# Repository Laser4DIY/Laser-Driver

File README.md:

# LASER4DIY Laser Diode Driver

Constant current power supply for laser diode to be used for the Laser4DIY project, see http://www.laser4diy.org/

Note: we are currently developing a new improved version of the laser diode driver, see https://github.com/Laser4DIY/Laser-Driver-v2

Copyright FabLab München e.V.  2021.

This source describes Open Hardware and is licensed under the CERN-OHL-P v2

You may redistribute and modify this documentation and make products using it 
under the terms of the CERN-OHL-P v2 (https:/cern.ch/cern-ohl).
This documentation is distributed WITHOUT ANY EXPRESS OR IMPLIED WARRANTY, 
INCLUDING OF MERCHANTABILITY, SATISFACTORY QUALITY AND FITNESS FOR A  PARTICULAR 
PURPOSE. Please see the CERN-OHL-P v2 for applicable conditions

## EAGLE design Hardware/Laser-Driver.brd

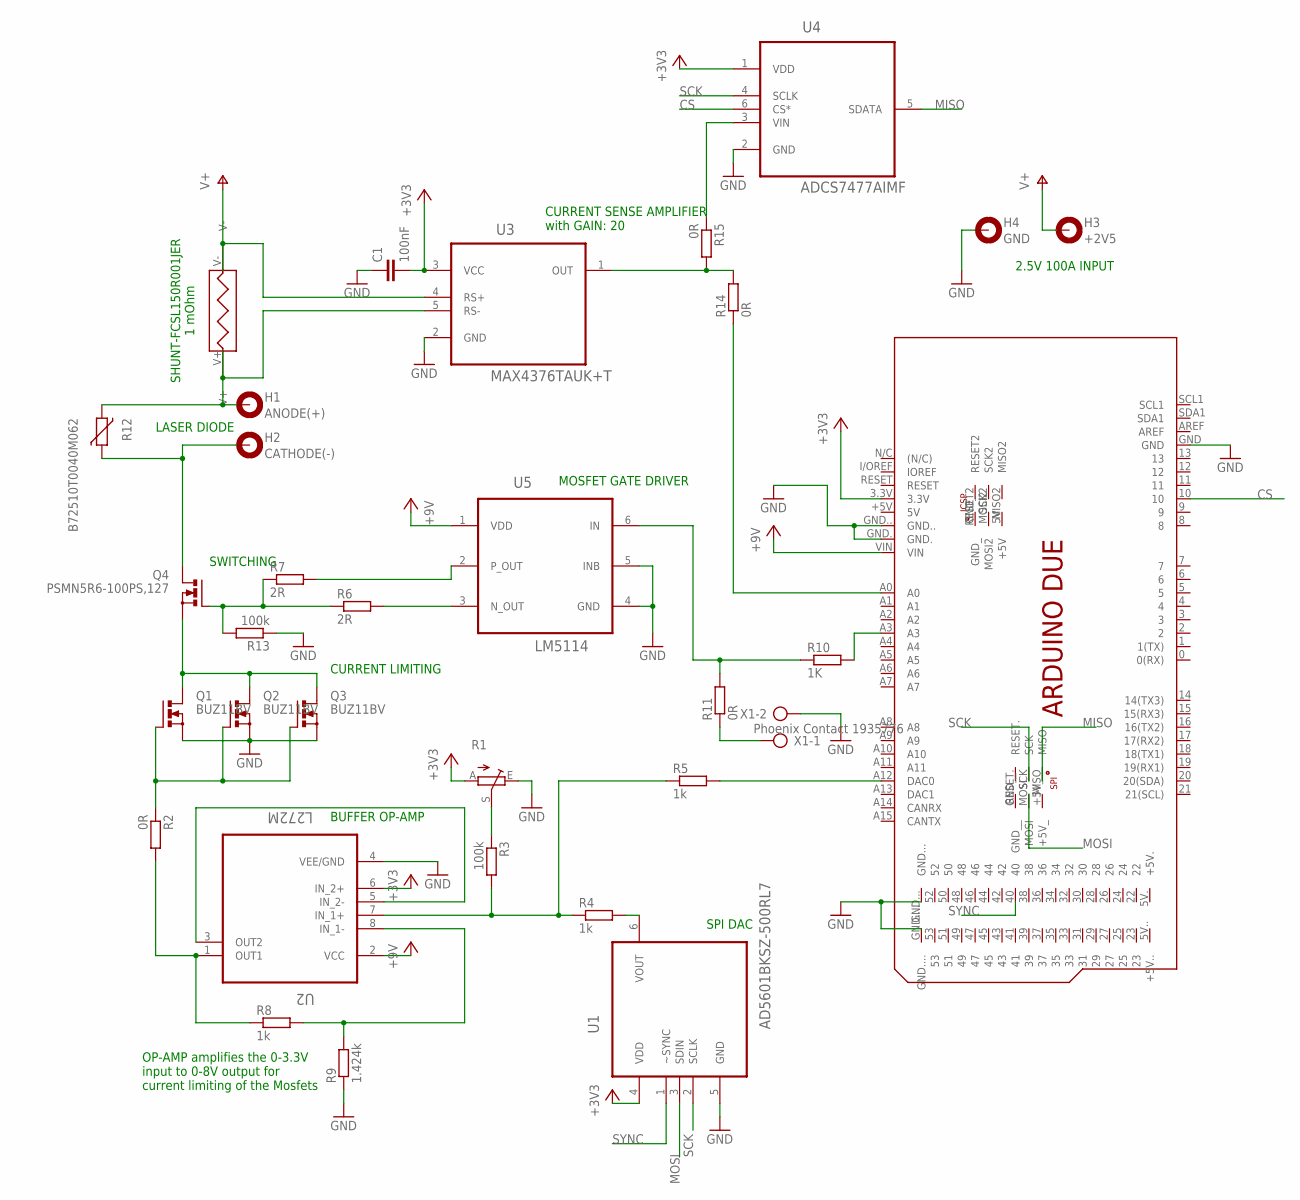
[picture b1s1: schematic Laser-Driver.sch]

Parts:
C1: 100nF; C0805
H1: ANODE(+); 3,2-PAD
H2: CATHODE(-); 3,2-PAD
H3: +2V5; 3,2-PAD
H4: GND; 3,2-PAD
PCB1: ARDUINO_DUE_SHIELD_SPI
Q1, Q2, Q3: BUZ11BV; TO220BV
Q4: PSMN5R6-100PS,127; TO220BV
R1: TRIM_EU-B64W; B64W
R2, R11, R14, R15: 0R; R0805
R3, R13: 100k; R0805
R4, R5, R8: 1k; R0805
R6, R7: 2R; R0805
R9: 1.424k; R0805
R10: 1K; R0805
R12: B72510T0040M062; CT/CN0805
U1: AD5601BKSZ-500RL7; SOT65P210X110-6N
U2: L272M; DIP254P762X508-8
U3: MAX4376TAUK+T; SOT95P280X145-5N
U4: ADCS7477AIMF; SOT95P280X145-6N
U5: LM5114; SOT95P280X145-6N
U$1: SHUNT-FCSL150R001-NOKELVIN
X1: Phoenix Contact 1935776; AK500/2

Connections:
+2V5: H3.B3,2, U3.4 (RS+), U$1.V-
+3V3: C1.2, PCB1.3.3V, R1.A, U1.4 (VDD), U2.6 (IN_2+), U3.3 (VCC), U4.1 (VDD)
+9V: PCB1.VIN, U2.2 (VCC), U5.1 (VDD)
CS: PCB1.10, U4.6 (CS*)
GND: C1.1, H4.B3,2, PCB1.GND, PCB1.GND., PCB1.GND.., PCB1.GND..., PCB1.GND...., Q1.S, Q2.S, Q3.S, R1.E, R9.1, R13.1, U1.5 (GND), U2.4 (VEE/GND), U3.2 (GND), U4.2 (GND), U5.4 (GND), U5.5 (INB), X1.2
MISO: PCB1.MISO, U4.5 (SDATA)
MOSI: PCB1.MOSI, U1.3 (SDIN)
unnamed: R7.2, U5.2 (P_OUT)
unnamed: H1.B3,2, R12.2, U3.5 (RS-), U$1.V+
unnamed: Q1.D, Q2.D, Q3.D, Q4.S
unnamed: R6.2, U5.3 (N_OUT)
unnamed: R2.2, R8.1, U2.1 (OUT1)
unnamed: Q1.G, Q2.G, Q3.G, R2.1
unnamed: U2.3 (OUT2), U2.5 (IN_2-)
unnamed: R3.2, R4.1, R5.1, U2.7 (IN_1+)
unnamed: R1.S, R3.1
unnamed: R4.2, U1.6 (VOUT)
unnamed: PCB1.A12 (DAC0), R5.2
unnamed: PCB1.A0, R14.1
unnamed: R8.2, R9.2, U2.8 (IN_1-)
unnamed: R10.1, R11.2, U5.6 (IN)
unnamed: PCB1.A3, R10.2
unnamed: R11.1, X1.1
unnamed: Q4.G, R6.1, R7.1, R13.2
unnamed: R14.2, R15.2, U3.1 (OUT)
unnamed: H2.B3,2, Q4.D, R12.1
unnamed: R15.1, U4.3 (VIN)
SCK: PCB1.SCK, U1.2 (SCLK), U4.4 (SCLK)
SYNC: PCB1.40, U1.1 (~SYNC)

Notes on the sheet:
SHUNT-FCSL150R001JER 1 mOhm
CURRENT SENSE AMPLIFIER with GAIN: 20
MOSFET GATE DRIVER
BUFFER OP-AMP
SPI DAC
LASER DIODE
2.5V 100A INPUT
OP-AMP amplifies the 0-3.3V input to 0-8V output for current limiting of the Mosfets
SWITCHING
CURRENT LIMITING

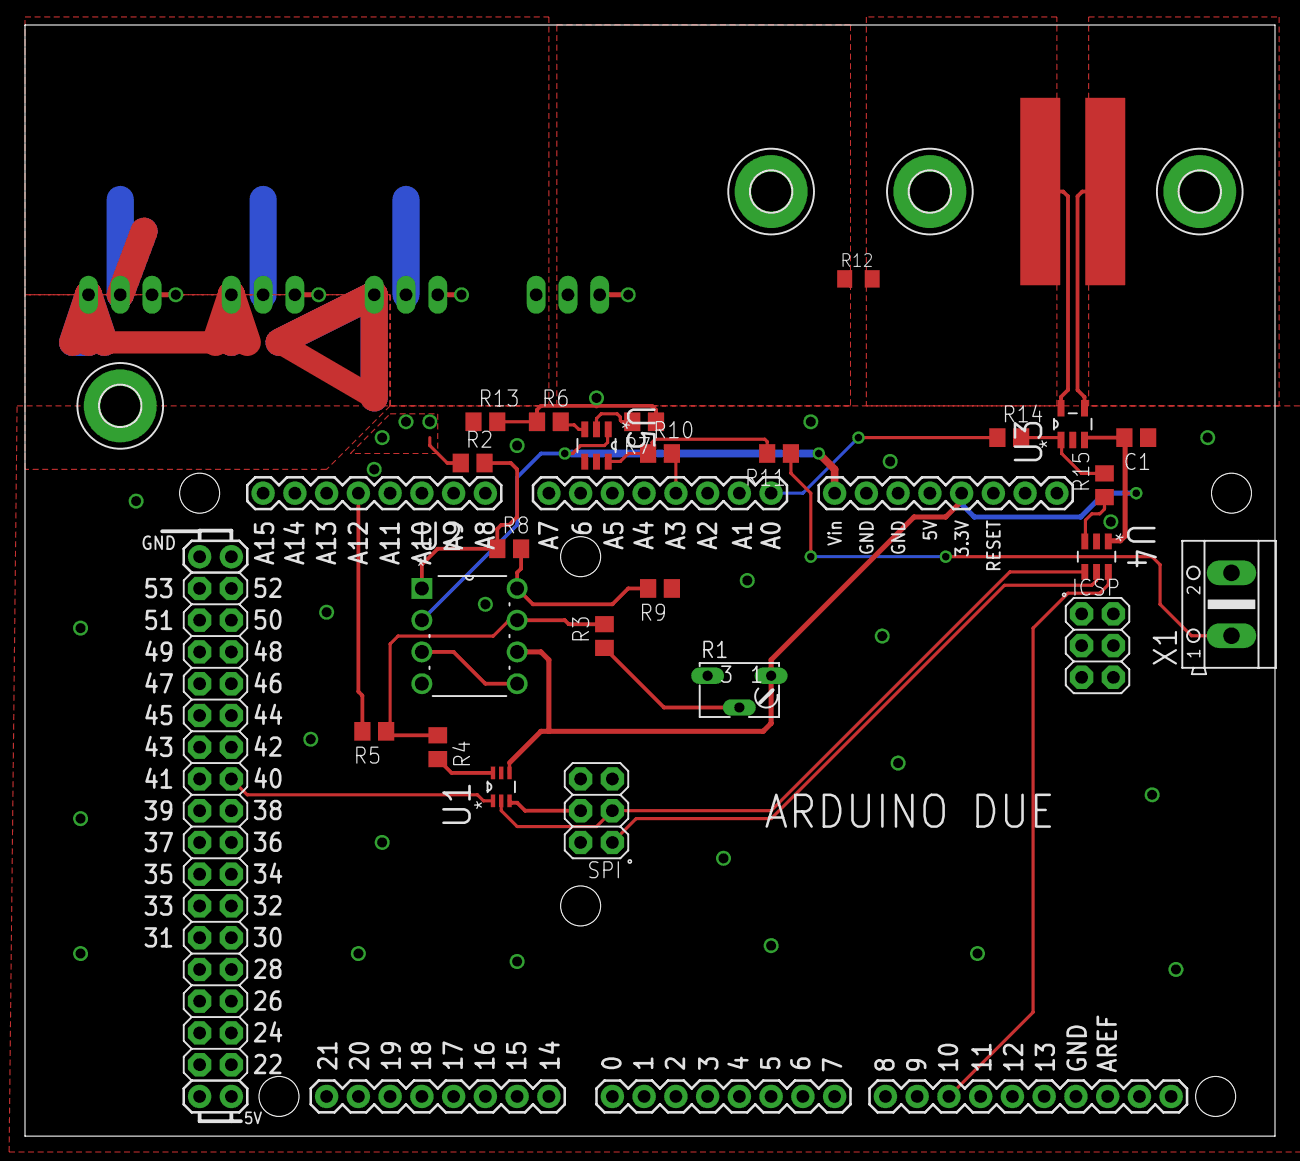
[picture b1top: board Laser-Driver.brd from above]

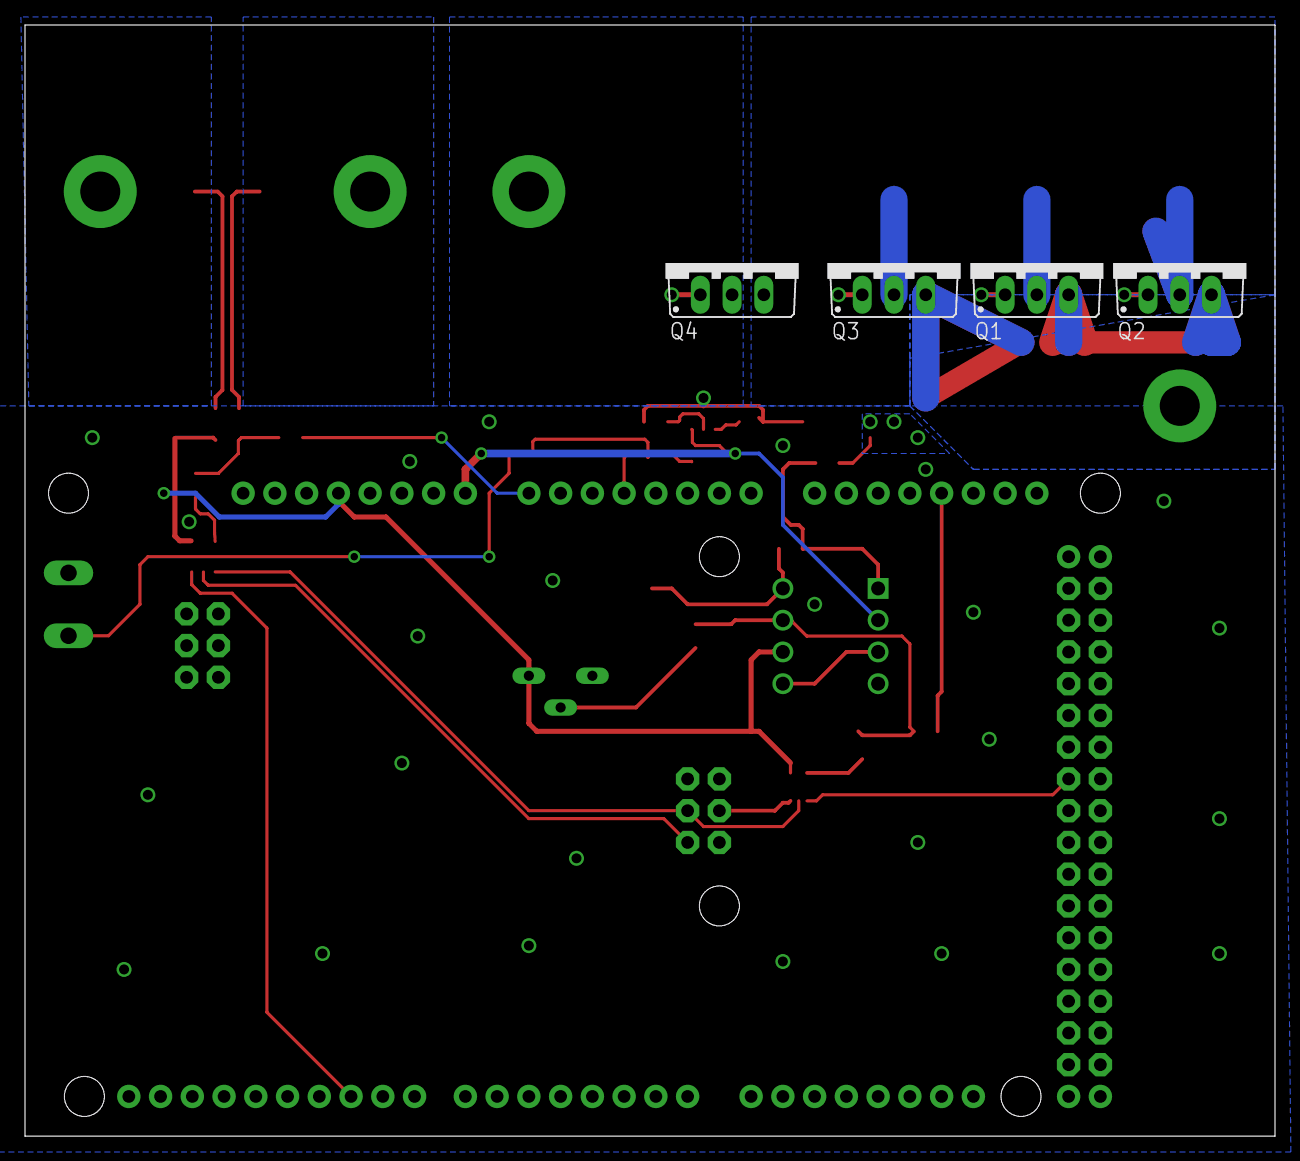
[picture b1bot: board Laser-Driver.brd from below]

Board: 2 copper layers, 100.0 x 88.9 mm, 32 parts (4 on the bottom side), 29 nets.

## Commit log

2018-03-29 initial release
    Testfirmware
2018-03-29 Revert "initial release"
    This reverts commit 8b9e5df8129df3e1c51870e52f897e7ae3e3be9e.
2018-03-29 initial commit
    This is a testversion
2021-02-19 added readme and license
